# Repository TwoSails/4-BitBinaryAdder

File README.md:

# 4-BitBinaryAdder
An electronics circuit to perform the basic addition of two 4-bit inputs designed on a PCB

The circuit was designed around the basic binary adder concept.

## IC Components 
Logical AND Gate: IC7408

Logical OR Gate: IC7432

Logical XOR Gate: IC7486

## Logic Diagram

## Circuit Diagram

## Notes by the Creator
This design isn't fully optimal, in particular PCB traces are capable of optimisations. It was the first full circuit design and PCB design endeavoured by myself and hence useful as a bedrock for future developments and projects with lots to learn from.

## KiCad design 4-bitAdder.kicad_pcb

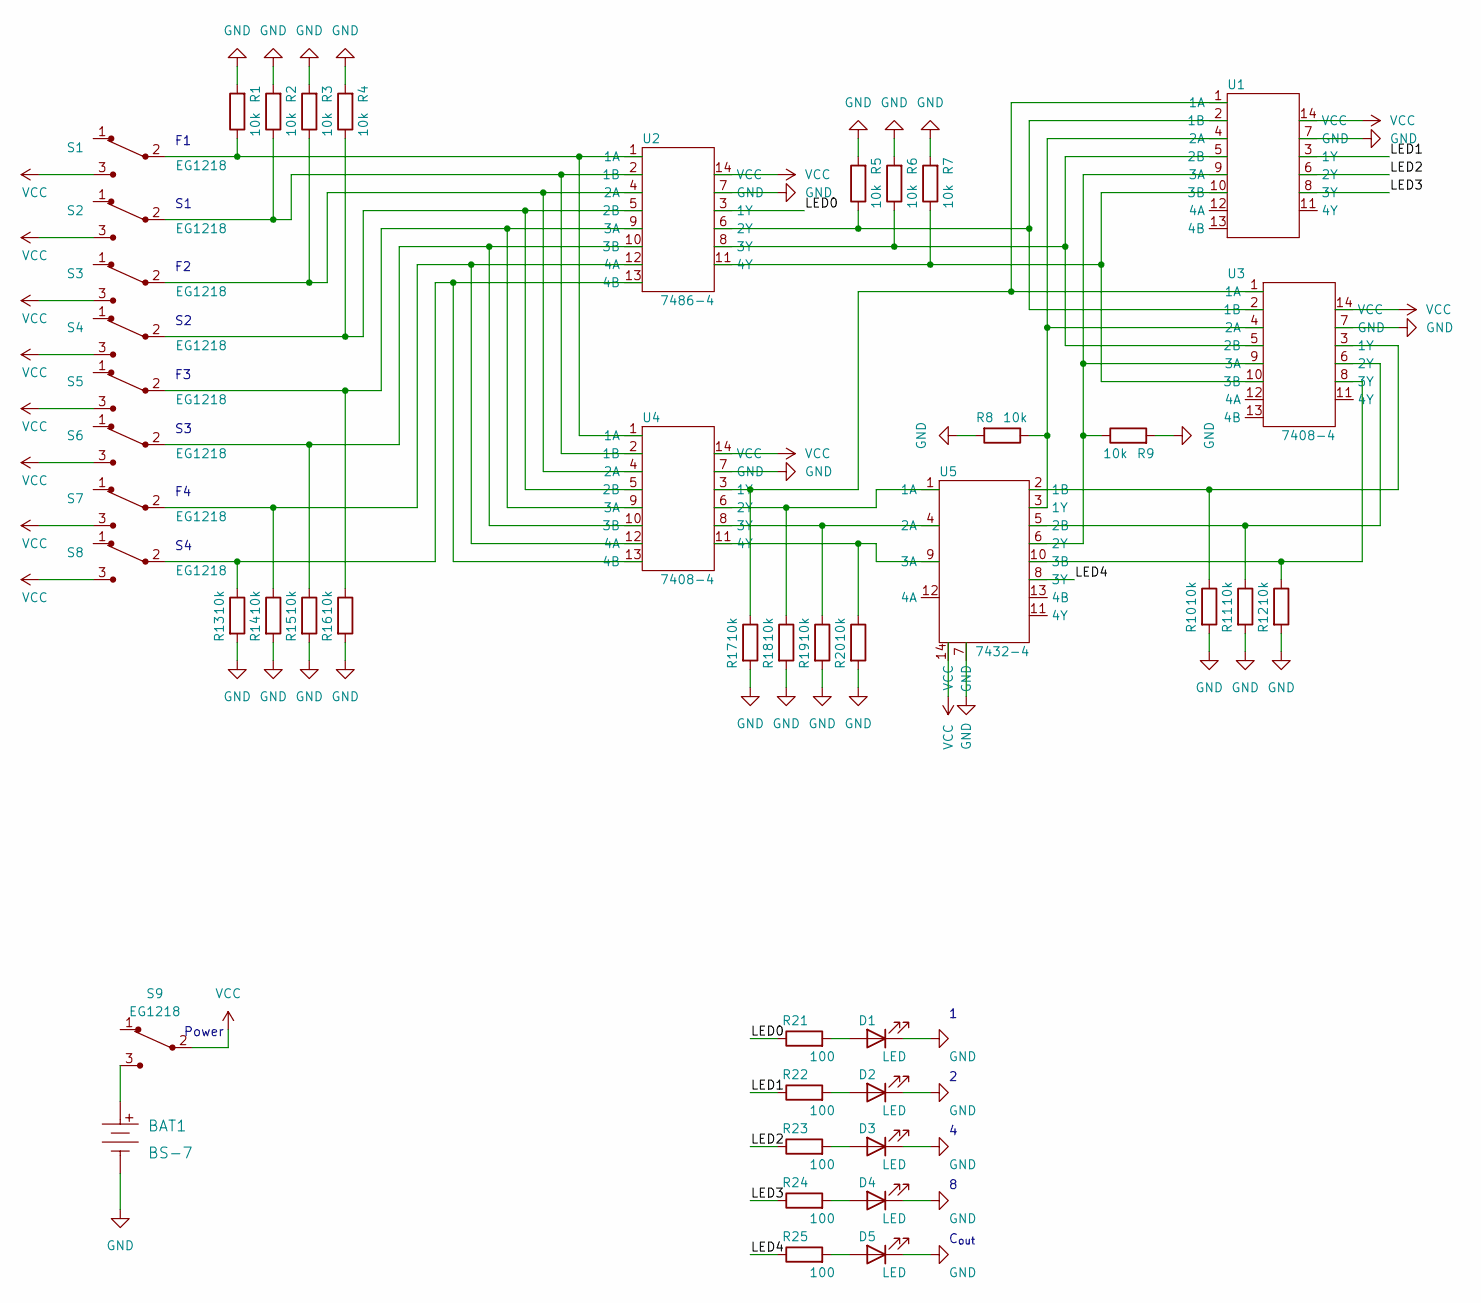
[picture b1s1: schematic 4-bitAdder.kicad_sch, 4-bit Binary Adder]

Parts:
BAT1: BS-7; Battery_Holder_Coin_2032_BS-7; MPN BS-7; Digi-Key_PN BS-7-ND
D1, D2, D3, D4, D5: LED; LED_D3.0mm
R1, R2, R3, R4, R5, R6, R7, R8, R9, R10, R11, R12, R13, R14, R15, R16, R17, R18, R19, R20: 10k; R_Axial_DIN0207_L6.3mm_D2.5mm_P7.62mm_Horizontal
R21, R22, R23, R24, R25: 100; R_Axial_DIN0207_L6.3mm_D2.5mm_P7.62mm_Horizontal
S1, S2, S3, S4, S5, S6, S7, S8, S9: EG1218; Switch_Slide_11.6x4mm_EG1218; MPN EG1218; Digi-Key_PN EG1903-ND
U1: (no value)
U2: 7486-4; IC7486-4-PDIP
U3, U4: 7408-4; IC7408-4-PDIP
U5: 7432-4; IC7432-4-PDIP

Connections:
/LED0: R21.1, U2.3 (1Y)
/LED1: R22.1, U1.3 (1Y)
/LED2: R23.1, U1.6 (2Y)
/LED3: R24.1, U1.8 (3Y)
/LED4: R25.1, U5.8 (3Y)
GND: BAT1.Neg, D1.1 (K), D2.1 (K), D3.1 (K), D4.1 (K), D5.1 (K), R1.2, R2.2, R3.2, R4.2, R5.2, R6.2, R7.2, R8.2, R9.2, R10.2, R11.2, R12.2, R13.2, R14.2, R15.2, R16.2, R17.2, R18.2, R19.2, R20.2, U1.7 (GND), U2.7 (GND), U3.7 (GND), U4.7 (GND), U5.7 (GND)
unnamed: BAT1.Pos, S9.3
unnamed: D1.2 (A), R21.2
unnamed: D2.2 (A), R22.2
unnamed: D3.2 (A), R23.2
unnamed: D4.2 (A), R24.2
unnamed: D5.2 (A), R25.2
unnamed: R1.1, S1.2, U2.1 (1A), U4.1 (1A)
unnamed: R2.1, S2.2, U2.2 (1B), U4.2 (1B)
unnamed: R3.1, S3.2, U2.4 (2A), U4.4 (2A)
unnamed: R4.1, S4.2, U2.5 (2B), U4.5 (2B)
unnamed: R5.1, U1.2 (1B), U2.6 (2Y), U3.2 (1B)
unnamed: R6.1, U1.5 (2B), U2.8 (3Y), U3.5 (2B)
unnamed: R7.1, U1.10 (3B), U2.11 (4Y), U3.10 (3B)
unnamed: R8.1, U1.4 (2A), U3.4 (2A), U5.3 (1Y)
unnamed: R9.1, U1.9 (3A), U3.9 (3A), U5.6 (2Y)
unnamed: R10.1, U3.3 (1Y), U5.2 (1B)
unnamed: R11.1, U3.6 (2Y), U5.5 (2B)
unnamed: R12.1, U3.8 (3Y), U5.10 (3B)
unnamed: R13.1, S8.2, U2.13 (4B), U4.13 (4B)
unnamed: R14.1, S7.2, U2.12 (4A), U4.12 (4A)
unnamed: R15.1, S6.2, U2.10 (3B), U4.10 (3B)
unnamed: R16.1, S5.2, U2.9 (3A), U4.9 (3A)
unnamed: R17.1, U1.1 (1A), U3.1 (1A), U4.3 (1Y)
unnamed: R18.1, U4.6 (2Y), U5.1 (1A)
unnamed: R19.1, U4.8 (3Y), U5.4 (2A)
unnamed: R20.1, U4.11 (4Y), U5.9 (3A)
VCC: S1.3, S2.3, S3.3, S4.3, S5.3, S6.3, S7.3, S8.3, S9.2, U1.14 (VCC), U2.14 (VCC), U3.14 (VCC), U4.14 (VCC), U5.14 (VCC)

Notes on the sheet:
Power
C_{out}

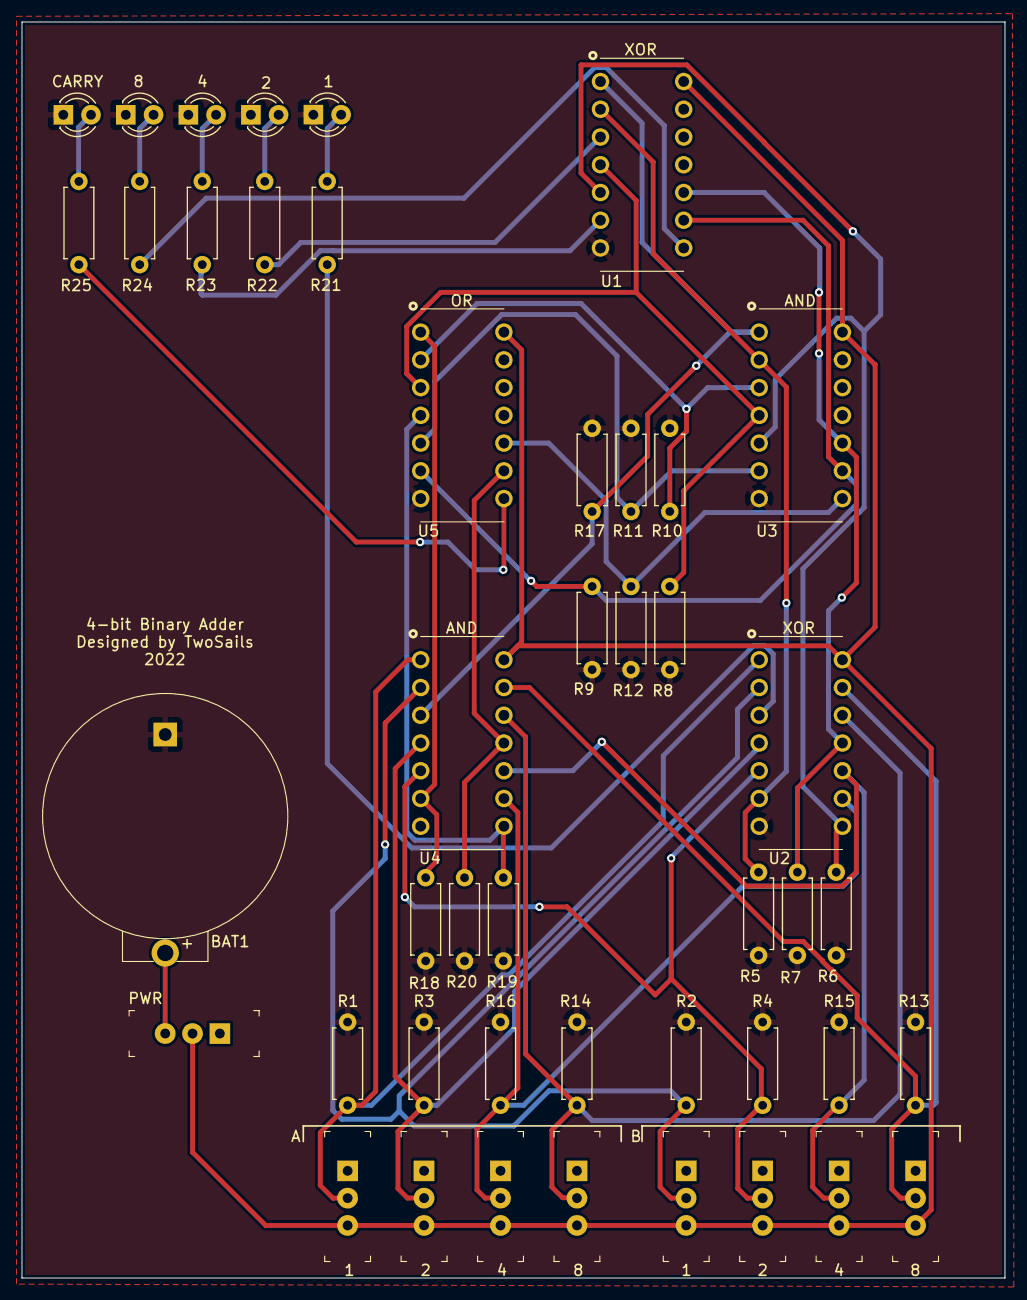
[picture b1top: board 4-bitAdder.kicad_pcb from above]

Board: 2 copper layers, 90.0 x 115.0 mm, 45 parts (0 on the bottom side), 33 nets.

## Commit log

2022-07-02 Added KiCad Files and Schematic Export
    Added Project Files and Gerber Files
2022-07-02 Added notes to the README

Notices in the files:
4-bitAdder.kicad_pcb:
https://creativecommons.org/licenses/by-sa/4.0
License: CC BY-SA 4.0
